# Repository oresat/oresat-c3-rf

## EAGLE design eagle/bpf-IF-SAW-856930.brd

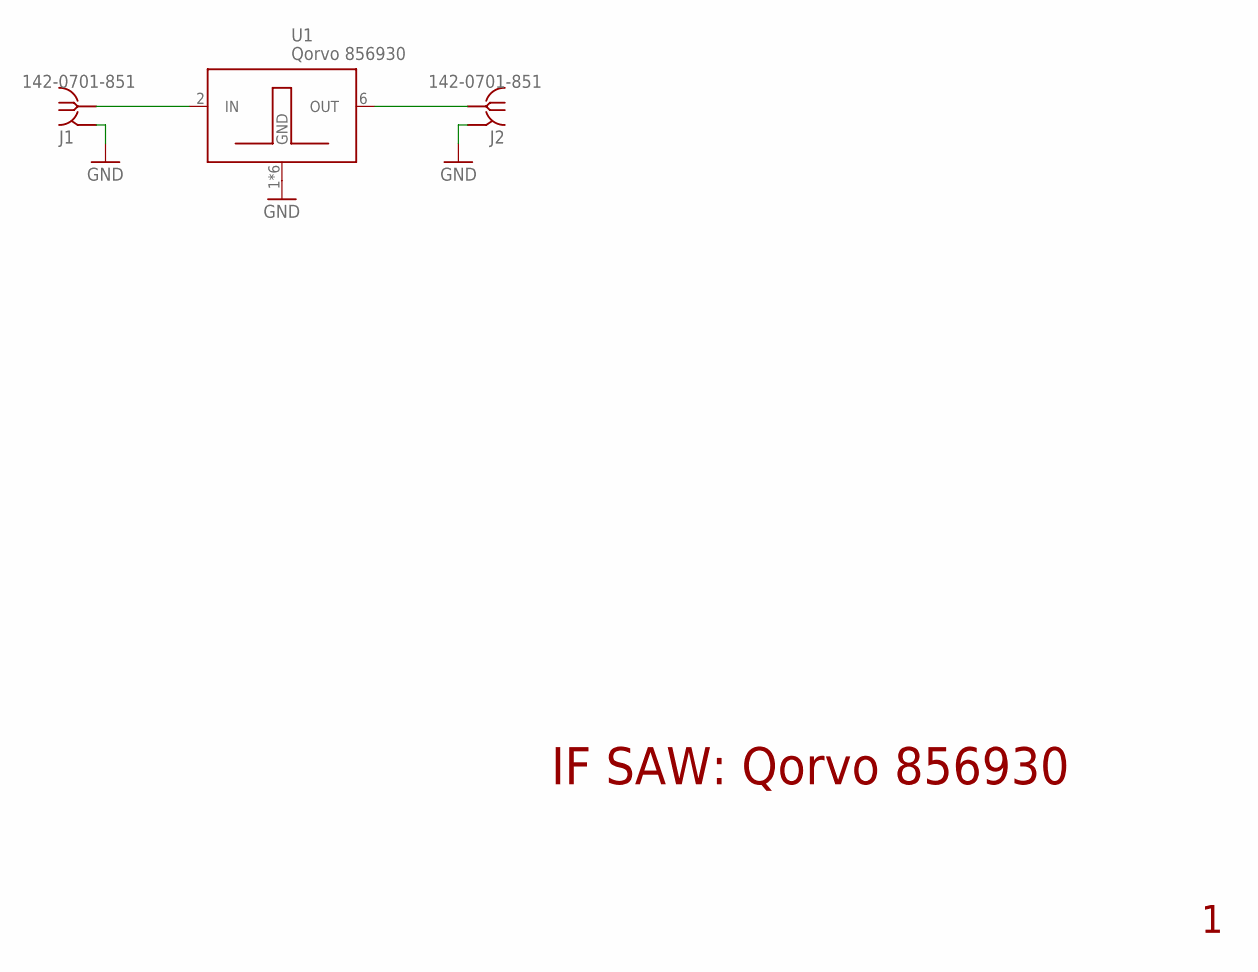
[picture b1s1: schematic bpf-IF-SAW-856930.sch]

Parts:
J1, J2: 142-0701-851
U1: Qorvo 856930; 3.8X3.8

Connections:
GND: J1.GND1 (GND), J1.GND2 (GND), J1.GND3 (GND), J1.GND4 (GND), J2.GND1 (GND), J2.GND2 (GND), J2.GND3 (GND), J2.GND4 (GND), U1.1 (GND), U1.3 (GND), U1.4 (GND), U1.5 (GND), U1.7 (GND), U1.8 (GND)
unnamed: J1.RF1 (RF), U1.2 (IN)
unnamed: J2.RF1 (RF), U1.6 (OUT)

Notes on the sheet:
IF SAW: Qorvo 856930

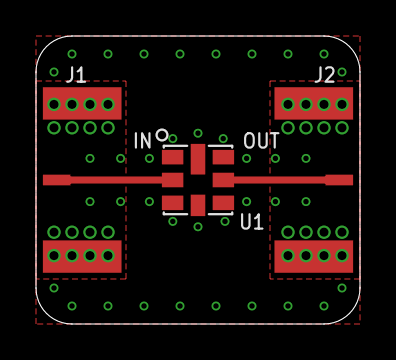
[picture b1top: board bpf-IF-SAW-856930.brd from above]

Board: 4 copper layers, 18.0 x 16.0 mm, 3 parts (0 on the bottom side), 3 nets.

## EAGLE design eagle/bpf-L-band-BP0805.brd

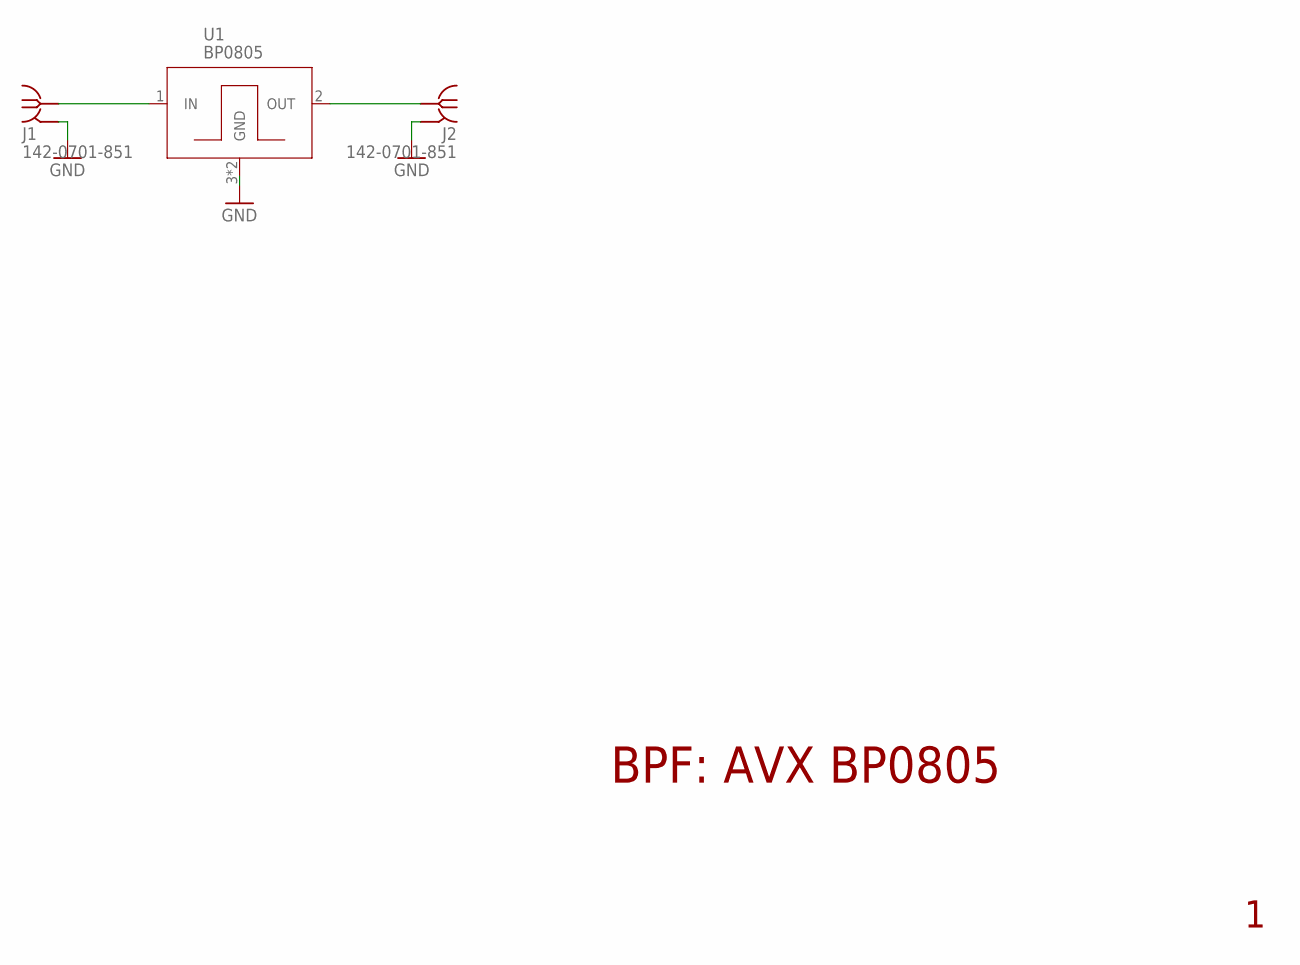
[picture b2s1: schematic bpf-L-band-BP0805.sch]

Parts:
J1, J2: 142-0701-851
U1: BP0805

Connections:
GND: J1.GND1 (GND), J1.GND2 (GND), J1.GND3 (GND), J1.GND4 (GND), J2.GND1 (GND), J2.GND2 (GND), J2.GND3 (GND), J2.GND4 (GND), U1.3 (GND), U1.4 (GND)
RF-IN: J1.RF1 (RF), U1.1 (IN)
RF-OUT: J2.RF1 (RF), U1.2 (OUT)

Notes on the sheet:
BPF: AVX BP0805

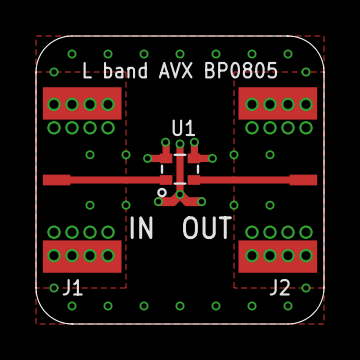
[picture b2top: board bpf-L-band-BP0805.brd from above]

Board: 4 copper layers, 16.0 x 16.0 mm, 3 parts (0 on the bottom side), 3 nets.

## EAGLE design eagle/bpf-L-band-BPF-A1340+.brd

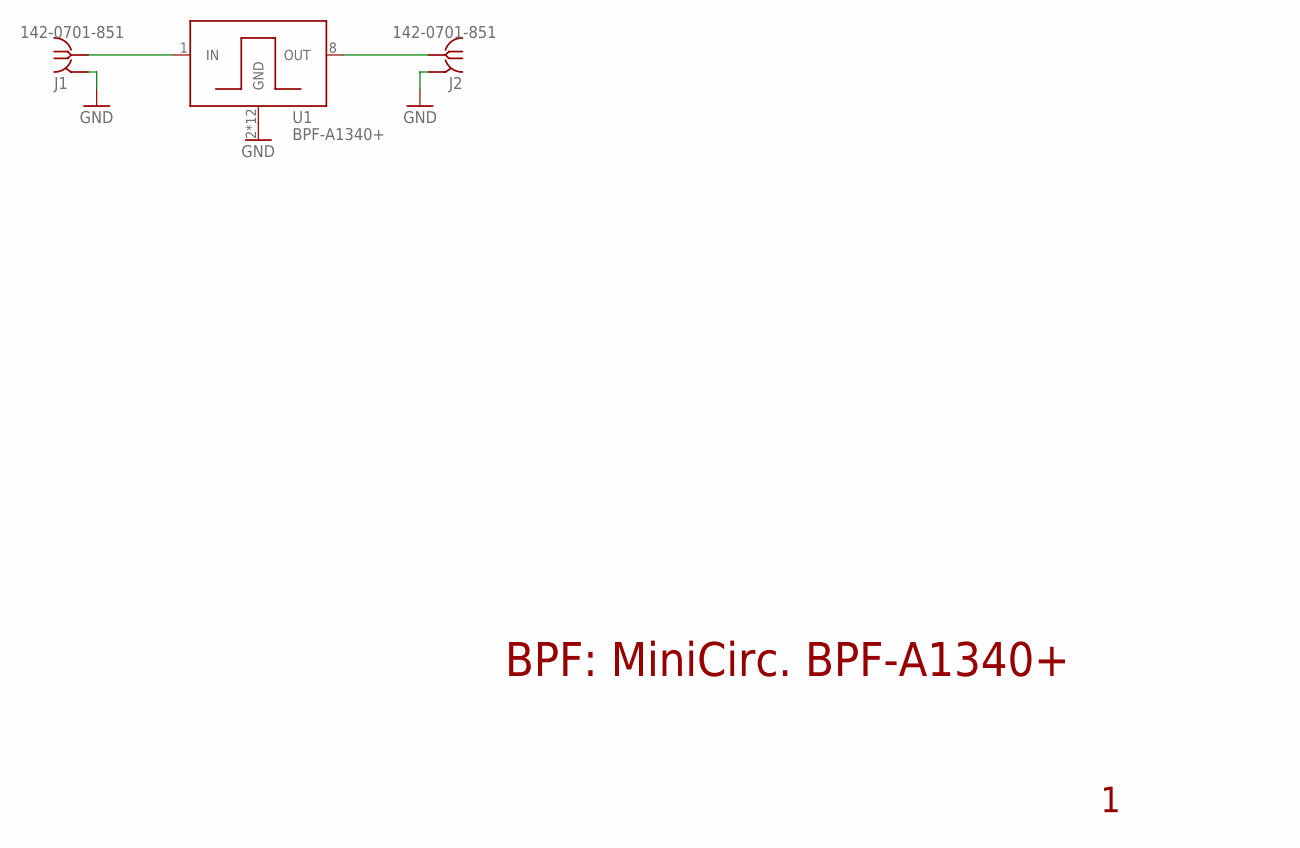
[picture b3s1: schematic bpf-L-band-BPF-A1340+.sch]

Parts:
J1, J2: 142-0701-851
U1: BPF-A1340+

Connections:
GND: J1.GND1 (GND), J1.GND2 (GND), J1.GND3 (GND), J1.GND4 (GND), J2.GND1 (GND), J2.GND2 (GND), J2.GND3 (GND), J2.GND4 (GND), U1.2 (GND), U1.3 (GND), U1.4 (GND), U1.5 (GND), U1.6 (GND), U1.7 (GND), U1.9 (GND), U1.10 (GND), U1.11 (GND), U1.12 (GND), U1.13 (GND), U1.14 (GND)
RF-IN: J1.RF1 (RF), U1.1 (IN)
RF-OUT: J2.RF1 (RF), U1.8 (OUT)

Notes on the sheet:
BPF: MiniCirc. BPF-A1340+

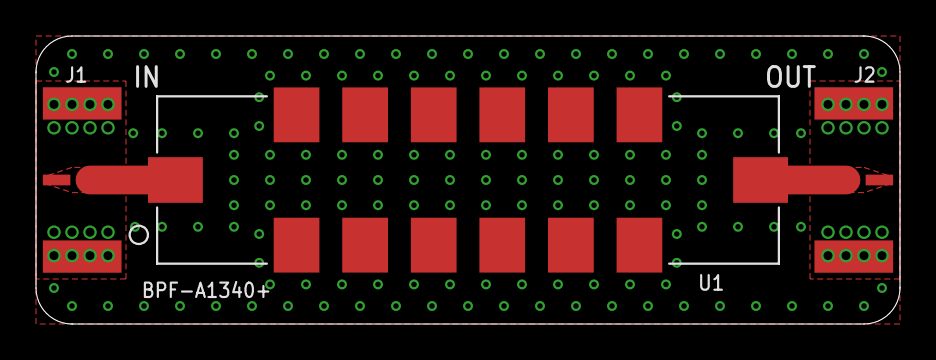
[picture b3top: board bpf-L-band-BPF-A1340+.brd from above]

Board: 2 copper layers, 48.0 x 16.0 mm, 3 parts (0 on the bottom side), 3 nets.

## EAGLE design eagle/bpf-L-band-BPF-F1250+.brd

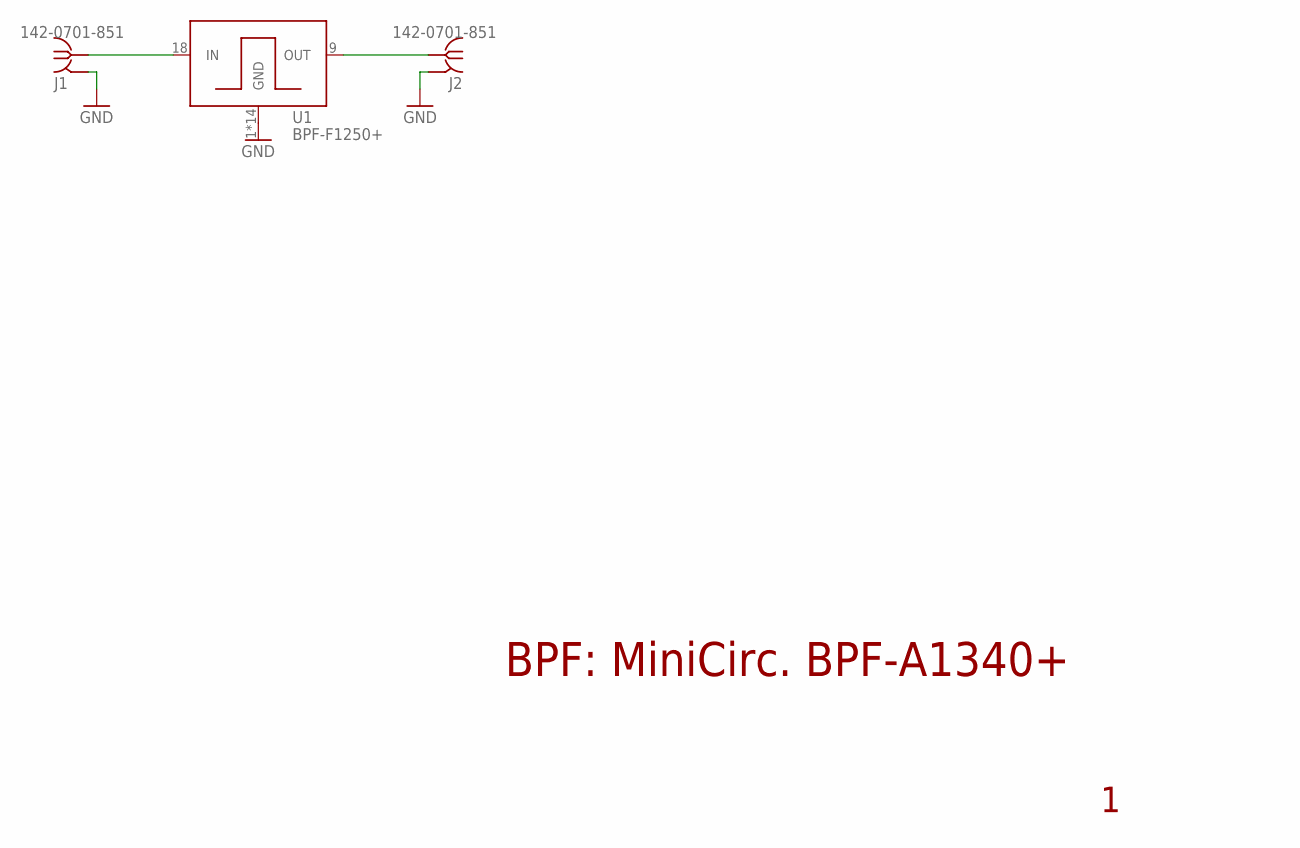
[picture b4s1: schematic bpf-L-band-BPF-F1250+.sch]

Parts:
J1, J2: 142-0701-851
U1: BPF-F1250+

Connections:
GND: J1.GND1 (GND), J1.GND2 (GND), J1.GND3 (GND), J1.GND4 (GND), J2.GND1 (GND), J2.GND2 (GND), J2.GND3 (GND), J2.GND4 (GND), U1.1 (GND), U1.3 (GND), U1.4 (GND), U1.5 (GND), U1.6 (GND), U1.7 (GND), U1.8 (GND), U1.10 (GND), U1.12 (GND), U1.13 (GND), U1.14 (GND), U1.15 (GND), U1.16 (GND), U1.17 (GND)
RF-IN: J1.RF1 (RF), U1.18 (IN)
RF-OUT: J2.RF1 (RF), U1.9 (OUT)

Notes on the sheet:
BPF: MiniCirc. BPF-A1340+

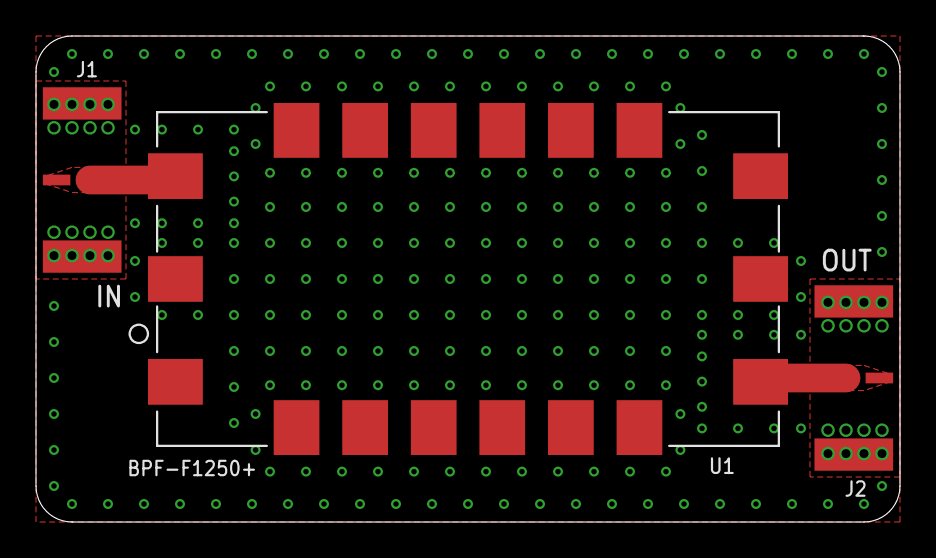
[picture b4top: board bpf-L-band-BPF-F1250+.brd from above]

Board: 2 copper layers, 48.0 x 27.0 mm, 3 parts (0 on the bottom side), 3 nets.

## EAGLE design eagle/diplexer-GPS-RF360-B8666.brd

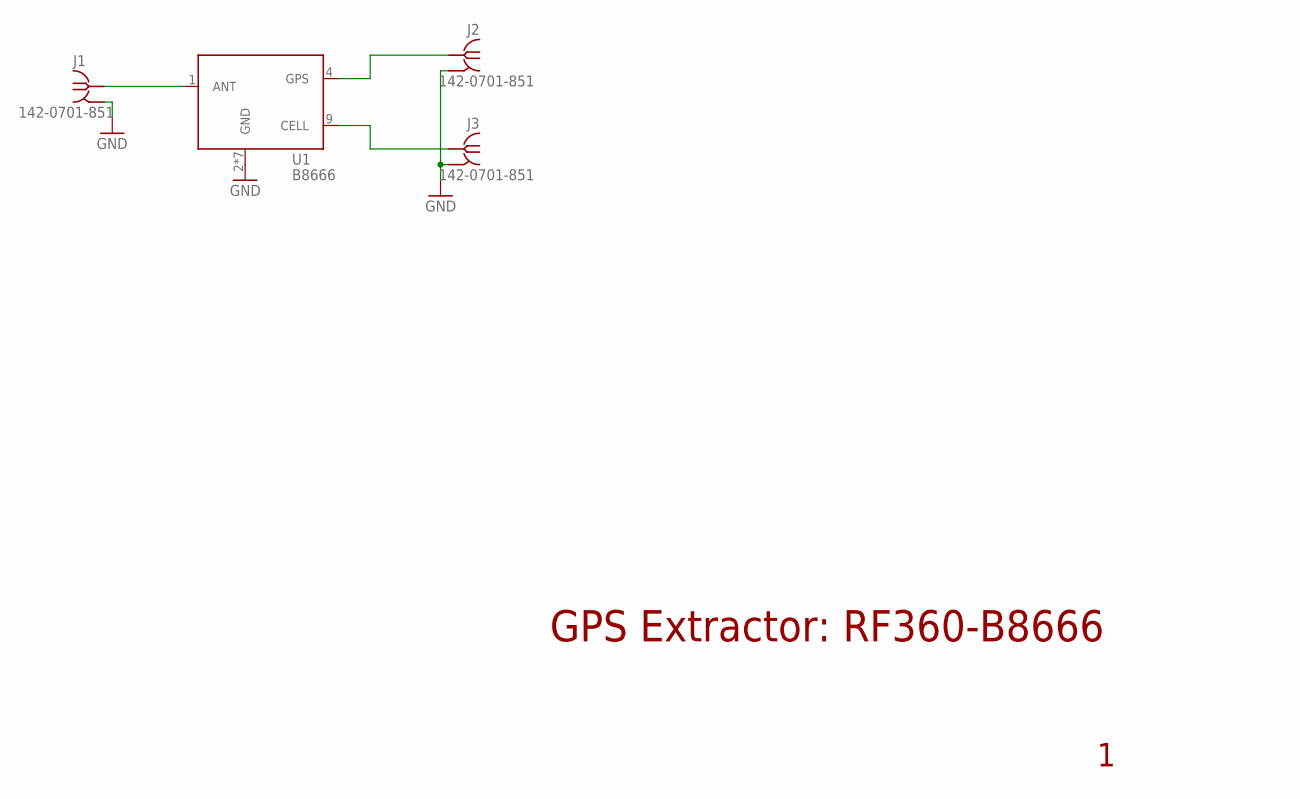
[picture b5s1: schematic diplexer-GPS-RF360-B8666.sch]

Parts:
J1, J2, J3: 142-0701-851
U1: B8666; 1.7X1.3

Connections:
GND: J1.GND1 (GND), J1.GND2 (GND), J1.GND3 (GND), J1.GND4 (GND), J2.GND1 (GND), J2.GND2 (GND), J2.GND3 (GND), J2.GND4 (GND), J3.GND1 (GND), J3.GND2 (GND), J3.GND3 (GND), J3.GND4 (GND), U1.2 (GND), U1.3 (GND), U1.5 (GND), U1.6 (GND), U1.7 (GND), U1.8 (GND), U1.10 (GND)
GPS: J2.RF1 (RF), U1.4 (GPS)
RF-IN: J1.RF1 (RF), U1.1 (ANT)
RF-OUT: J3.RF1 (RF), U1.9 (CELL)

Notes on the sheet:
GPS Extractor: RF360-B8666

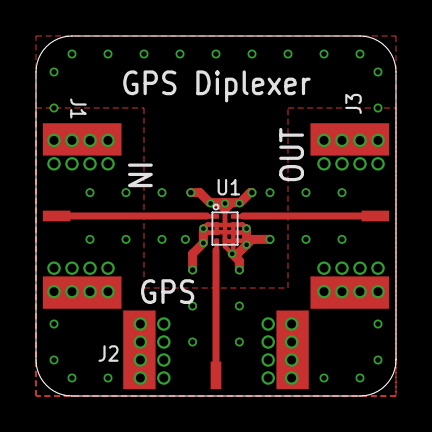
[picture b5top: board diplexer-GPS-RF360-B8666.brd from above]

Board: 4 copper layers, 20.0 x 20.0 mm, 4 parts (0 on the bottom side), 4 nets.

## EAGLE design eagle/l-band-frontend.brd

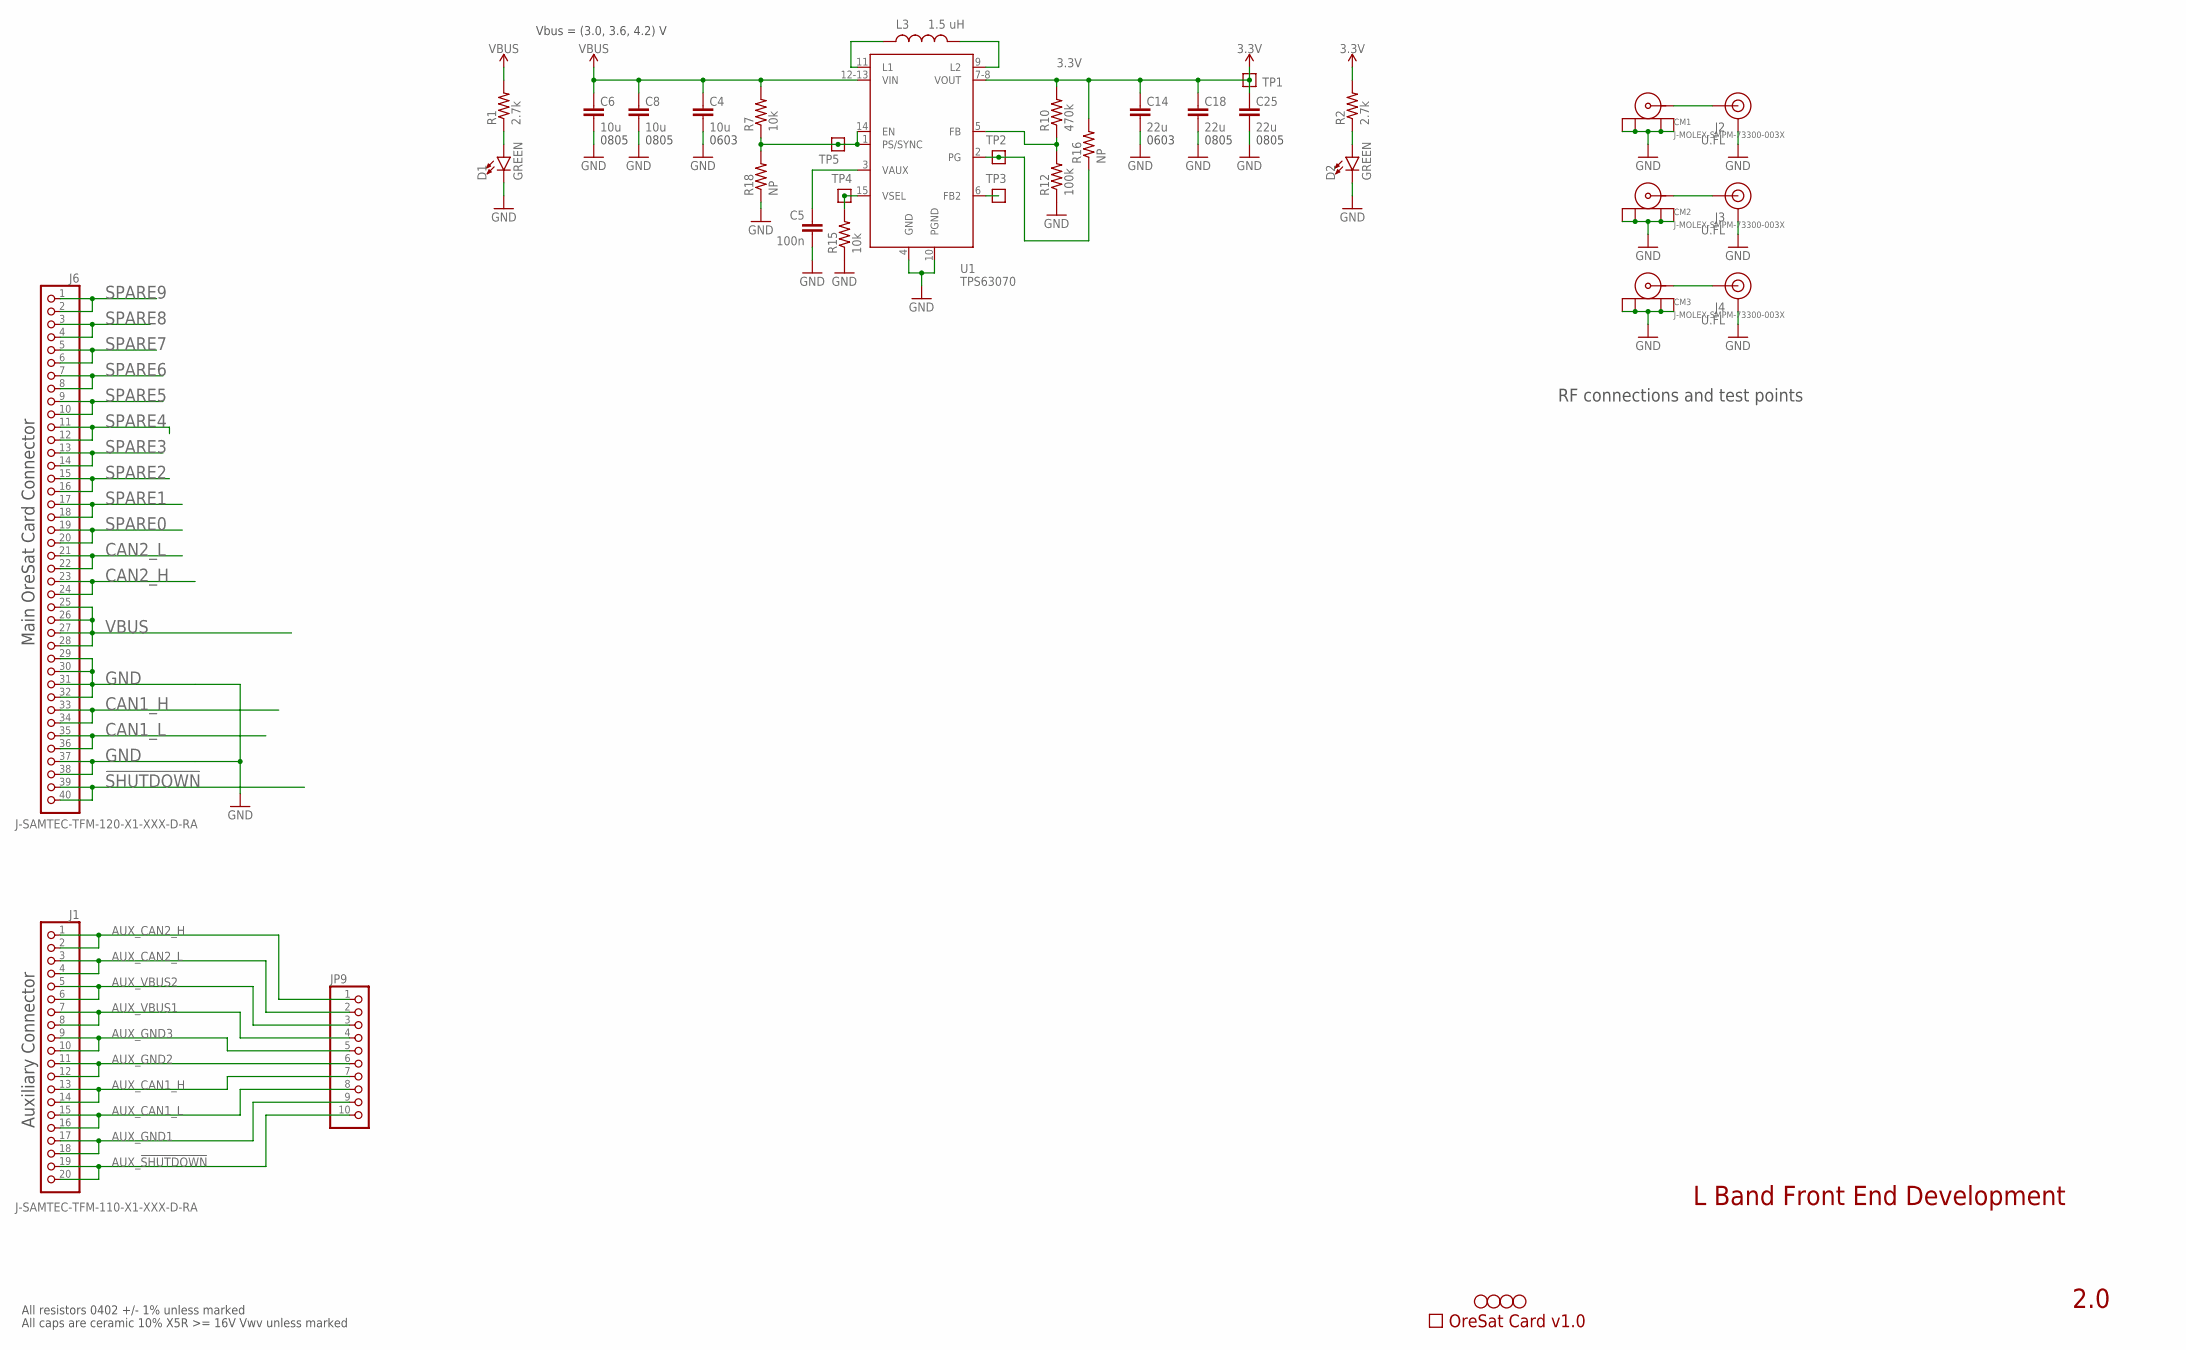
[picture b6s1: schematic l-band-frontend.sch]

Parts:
C4: 10u; .0603-B-NOSILK; MPN CL05B104KO5NNNC
C5: 100n; .0402-B-NOSILK; MPN CL05B104KO5NNNC
C6, C8: 10u; .0805-B-NOSILK
C14: 22u; .0603-B-NOSILK; MPN CL05B104KO5NNNC
C18, C25: 22u; .0805-B-NOSILK
CARD: ORESAT-CARD-V0.5; ORESAT-CARD-V1.0
CM1, CM2, CM3: J-MOLEX-SMPM-73300-003X; J-MOLEX-SMPM-073300-003X
D1, D2: GREEN; LED-0603
H1, H2, H3, H4: STAND-OFFTIGHT; STAND-OFF-TIGHT
J1: J-SAMTEC-TFM-110-X1-XXX-D-RA; MPN TFM-110-01-L-D-RA
J2, J3, J4: U.FL
J6: J-SAMTEC-TFM-120-X1-XXX-D-RA; MPN TFM-120-01-L-D-RA
JP9: PINHD-1X10; 1X10
L3: 1.5 uH; L-COILCRAFT-XFL4020; MPN XFL4020-152ME
R1, R2: 2.7k; .0402-B-NOSILK; MPN RC1005F6653CS
R7, R15: 10k; .0402-B-NOSILK; MPN RC1005F6653CS
R10: 470k; .0402-B-NOSILK; MPN RC1005F6653CS
R12: 100k; .0402-B-NOSILK; MPN RC1005F6653CS
R16, R18: NP; .0402-B-NOSILK; MPN RC1005F6653CS
TP1, TP2, TP3, TP4, TP5: TEST-POINT; 2MM-TEST-POINT
U1: TPS63070; TPS63070X; MPN TPS63070

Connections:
3.3V: C14.1, C18.1, C25.1, R2.2, R10.2, R16.2, TP1.1, U1.7-8 (VOUT)
!SHUTDOWN: J6.39, J6.40
AUX_!SHUTDOWN: J1.19, J1.20, JP9.10
AUX_CAN1_H: J1.13, J1.14, JP9.7
AUX_CAN1_L: J1.15, J1.16, JP9.8
AUX_CAN2_H: J1.1, J1.2, JP9.1
AUX_CAN2_L: J1.3, J1.4, JP9.2
AUX_GND1: J1.17, J1.18, JP9.9
AUX_GND2: J1.11, J1.12, JP9.6
AUX_GND3: J1.9, J1.10, JP9.5
AUX_VBUS1: J1.7, J1.8, JP9.4
AUX_VBUS2: J1.5, J1.6, JP9.3
CAN1_H: J6.33, J6.34
CAN1_L: J6.35, J6.36
CAN2_H: J6.23, J6.24
CAN2_L: J6.21, J6.22
GND: C4.2, C5.2, C6.2, C8.2, C14.2, C18.2, C25.2, CM1.P$1 (SHIELD3), CM1.P$2 (SHIELD2), CM1.P$3 (SHIELD1), CM1.P$4 (SHIELD), CM2.P$1 (SHIELD3), CM2.P$2 (SHIELD2), CM2.P$3 (SHIELD1), CM2.P$4 (SHIELD), CM3.P$1 (SHIELD3), CM3.P$2 (SHIELD2), CM3.P$3 (SHIELD1), CM3.P$4 (SHIELD), D1.C, D2.C, J2.1 (GND), J2.2 (GND), J3.1 (GND), J3.2 (GND), J4.1 (GND), J4.2 (GND), J6.29, J6.30, J6.31, J6.32, J6.37, J6.38, R12.1, R15.1, R18.1, U1.4 (GND), U1.10 (PGND)
unnamed: D1.A, R1.1
unnamed: D2.A, R2.1
unnamed: CM3.RF (CENTER), J4.FEED (SIGNAL)
RF1: CM1.RF (CENTER), J2.FEED (SIGNAL)
RF2: CM2.RF (CENTER), J3.FEED (SIGNAL)
SPARE0: J6.19, J6.20
SPARE1: J6.17, J6.18
SPARE2: J6.15, J6.16
SPARE3: J6.13, J6.14
SPARE4: J6.11, J6.12
SPARE5: J6.9, J6.10
SPARE6: J6.7, J6.8
SPARE7: J6.5, J6.6
SPARE8: J6.3, J6.4
SPARE9: J6.1, J6.2
TPS-EN1: R7.1, R18.2, TP5.1, U1.1 (PS/SYNC), U1.14 (EN)
TPS-FB1: R10.1, R12.2, U1.5 (FB)
TPS-FB3: TP3.1, U1.6 (FB2)
TPS-L3: L3.1, U1.11 (L1)
TPS-L4: L3.2, U1.9 (L2)
TPS-PG1: R16.1, TP2.1, U1.2 (PG)
TPS-VAUX1: C5.1, U1.3 (VAUX)
TPS-VSEL1: R15.2, TP4.1, U1.15 (VSEL)
VBUS: C4.1, C6.1, C8.1, J6.25, J6.26, J6.27, J6.28, R1.2, R7.2, U1.12-13 (VIN)

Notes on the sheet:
L Band Front End Development
2.0
All resistors 0402 +/- 1% unless marked
All caps are ceramic 10% X5R >= 16V Vwv unless marked
0603
0805
Auxiliary Connector
Main OreSat Card Connector
RF connections and test points
Vbus = (3.0, 3.6, 4.2) V

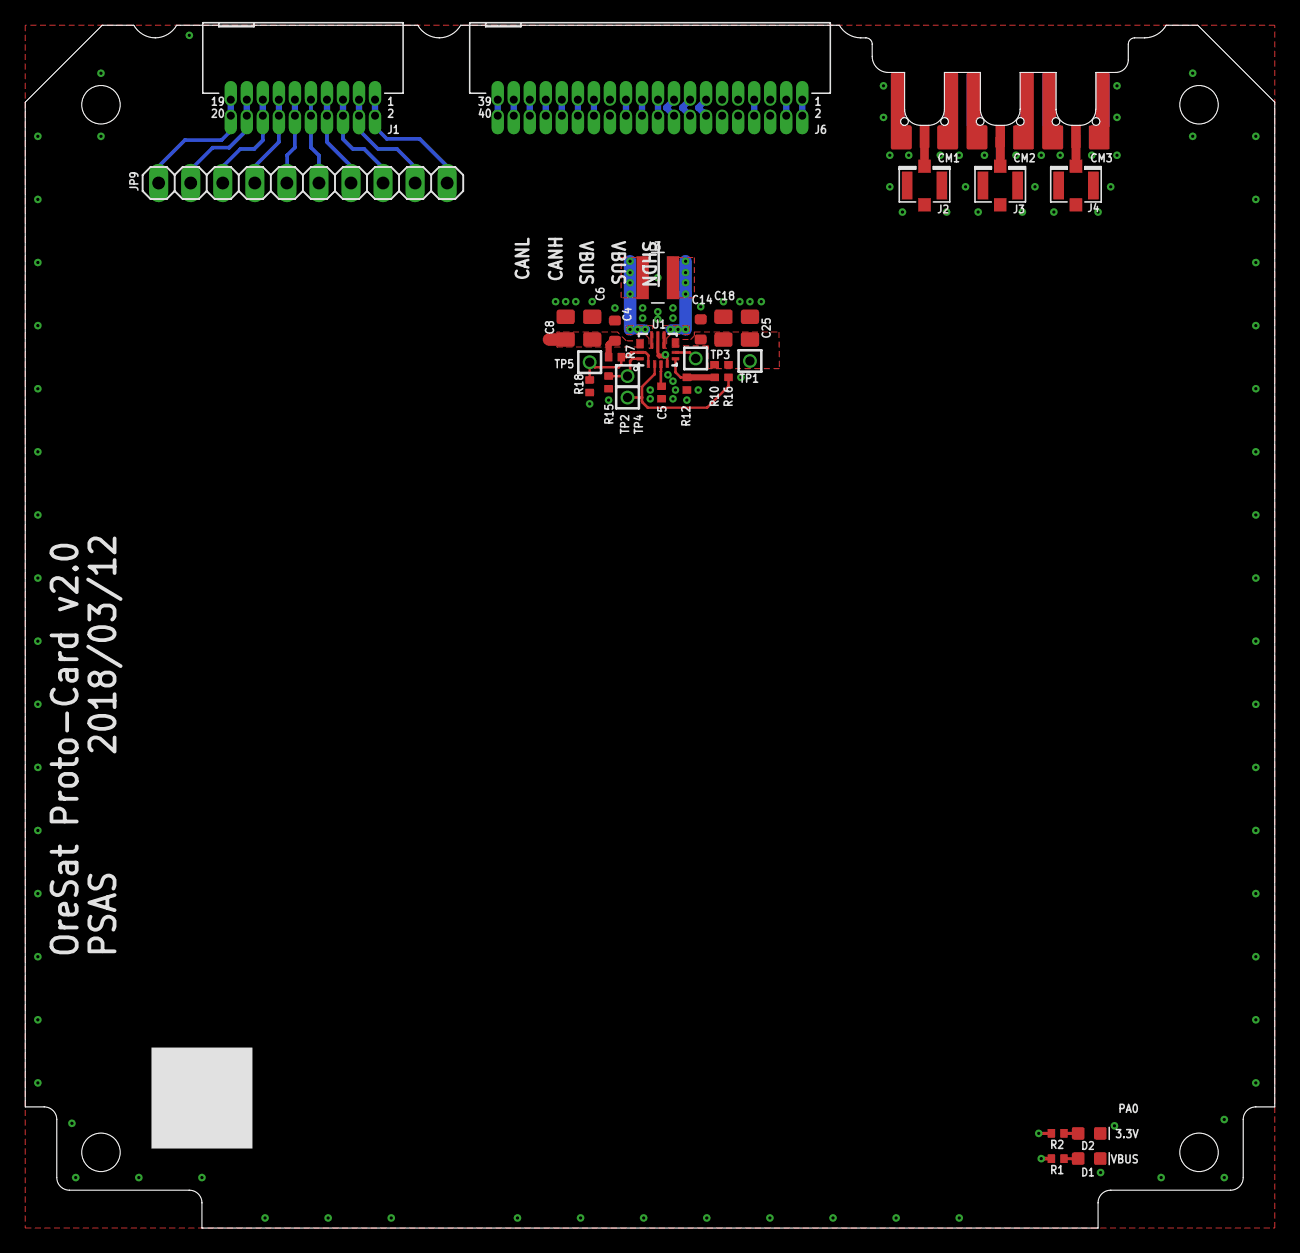
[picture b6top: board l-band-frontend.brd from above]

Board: 2 copper layers, 99.0 x 95.3 mm, 38 parts (0 on the bottom side), 41 nets.

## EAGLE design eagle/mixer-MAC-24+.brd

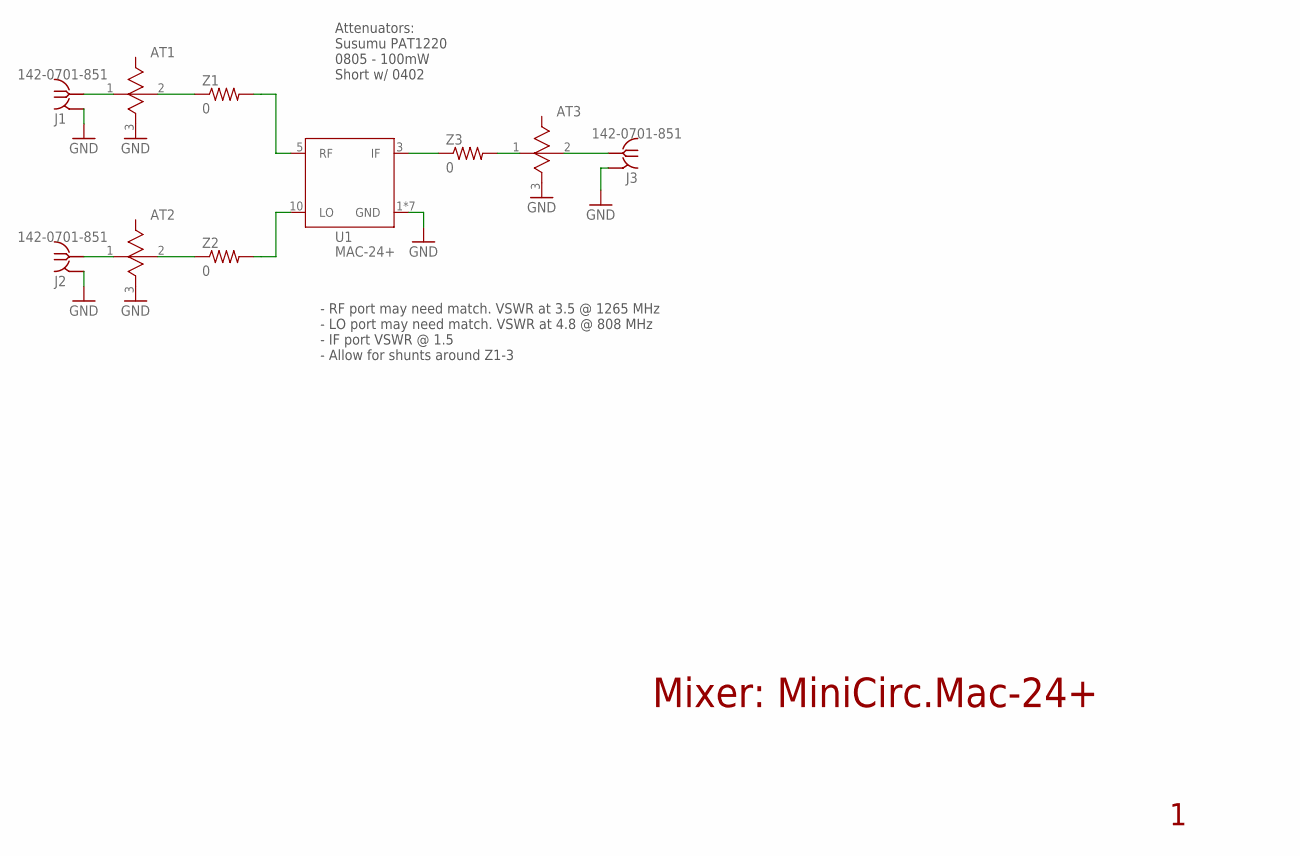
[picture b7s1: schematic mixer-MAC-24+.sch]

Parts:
AT1, AT2, AT3: PAT1220; 0805
J1, J2, J3: 142-0701-851
U1: MAC-24+
Z1, Z2, Z3: 0; .0402-C-NOSILK

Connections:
GND: AT1.3 (GND), AT2.3 (GND), AT3.3 (GND), J1.GND1 (GND), J1.GND2 (GND), J1.GND3 (GND), J1.GND4 (GND), J2.GND1 (GND), J2.GND2 (GND), J2.GND3 (GND), J2.GND4 (GND), J3.GND1 (GND), J3.GND2 (GND), J3.GND3 (GND), J3.GND4 (GND), U1.1 (GND), U1.2 (GND), U1.4 (GND), U1.6 (GND), U1.7 (GND), U1.8 (GND), U1.9 (GND)
IF: AT3.2, J3.RF1 (RF)
LO: AT2.1, J2.RF1 (RF)
unnamed: U1.3 (IF), Z3.1
unnamed: U1.5 (RF), Z1.2
unnamed: U1.10 (LO), Z2.2
unnamed: AT2.2, Z2.1
unnamed: AT1.2, Z1.1
unnamed: AT3.1, Z3.2
RF: AT1.1, J1.RF1 (RF)

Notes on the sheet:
Mixer: MiniCirc.Mac-24+
- RF port may need match. VSWR at 3.5 @ 1265 MHz - LO port may need match. VSWR at 4.8 @ 808 MHz - IF port VSWR @ 1.5 - Allow for shunts around Z1-3
Attenuators: Susumu PAT1220 0805 - 100mW Short w/ 0402

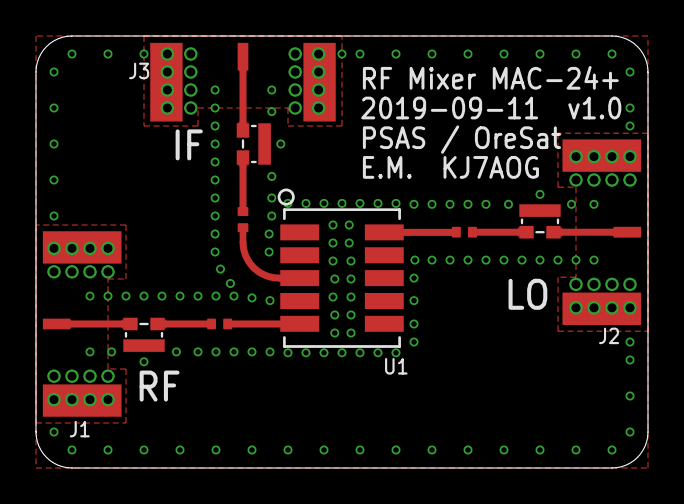
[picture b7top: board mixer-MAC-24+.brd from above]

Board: 4 copper layers, 34.0 x 24.0 mm, 10 parts (0 on the bottom side), 10 nets.

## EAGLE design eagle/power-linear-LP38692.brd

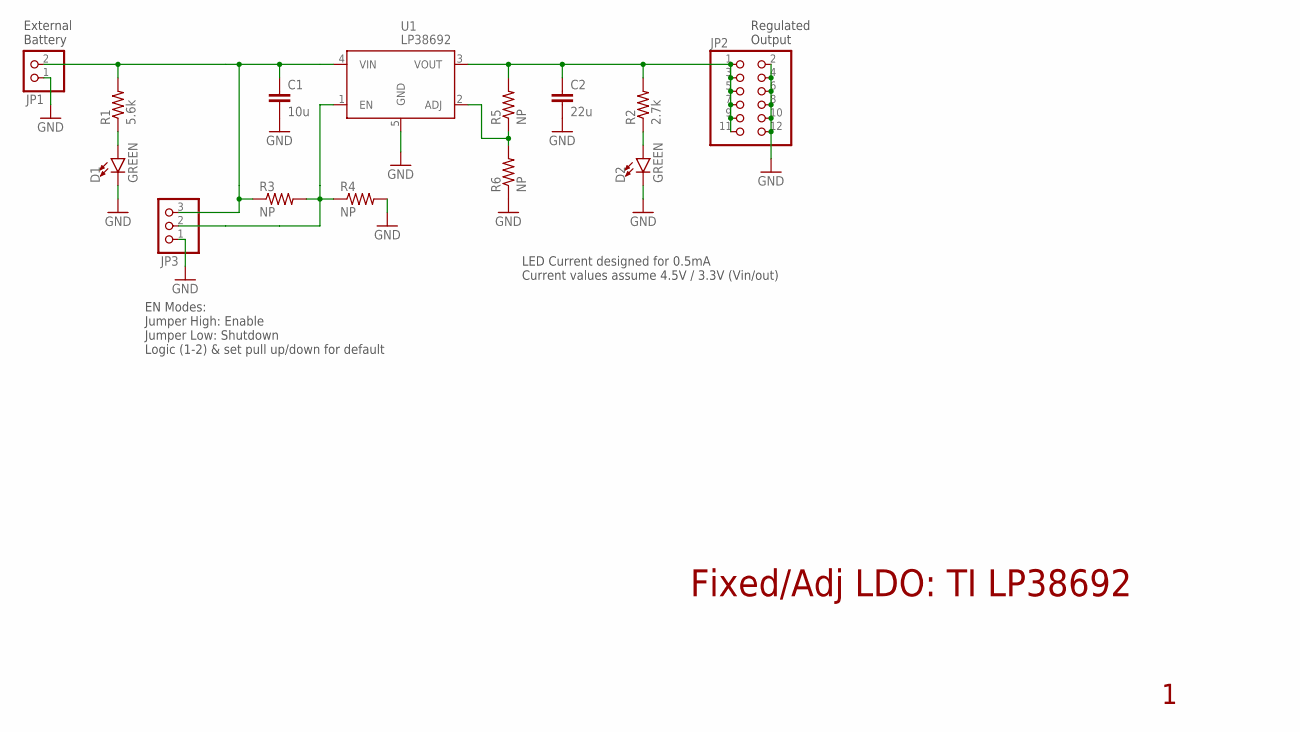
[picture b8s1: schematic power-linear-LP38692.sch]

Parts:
C1: 10u; .0805-B-NOSILK
C2: 22u; 1206-B
D1, D2: GREEN; LED-0603
JP1: PINHD-1X2; 1X02
JP2: PINHD-2X6; 2X06
JP3: PINHD-1X3; 1X03
R1: 5.6k; .0603-B-NOSILK
R2: 2.7k; .0603-B-NOSILK
R3, R4, R5, R6: NP; .0402-B-NOSILK
U1: LP38692; SOT223-5

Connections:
+VBAT: C1.1, JP1.2, JP3.3, R1.2, R3.1, U1.4 (VIN)
+VOUT: C2.1, JP2.1, JP2.3, JP2.5, JP2.7, JP2.9, JP2.11, R2.2, R5.2, U1.3 (VOUT)
GND: C1.2, C2.2, D1.C, D2.C, JP1.1, JP2.2, JP2.4, JP2.6, JP2.8, JP2.10, JP2.12, JP3.1, R4.2, R6.1, U1.5 (GND)
unnamed: R5.1, R6.2, U1.2 (ADJ)
unnamed: JP3.2, R3.2, R4.1, U1.1 (EN)
unnamed: D1.A, R1.1
unnamed: D2.A, R2.1

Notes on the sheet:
Fixed/Adj LDO: TI LP38692
External Battery
Regulated Output
EN Modes: Jumper High: Enable Jumper Low: Shutdown Logic (1-2) & set pull up/down for default
LED Current designed for 0.5mA Current values assume 4.5V / 3.3V (Vin/out)

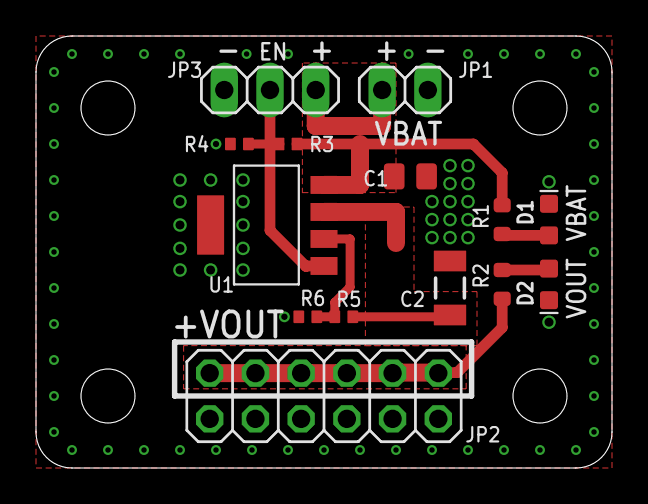
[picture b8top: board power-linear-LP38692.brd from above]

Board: 2 copper layers, 32.0 x 24.0 mm, 14 parts (0 on the bottom side), 7 nets.

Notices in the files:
parts and their libraries:
SparkFun-Connectors: Licensing: Creative Commons ShareAlike 4.0 International - https://creativecommons.org/licenses/by-sa/4.0
